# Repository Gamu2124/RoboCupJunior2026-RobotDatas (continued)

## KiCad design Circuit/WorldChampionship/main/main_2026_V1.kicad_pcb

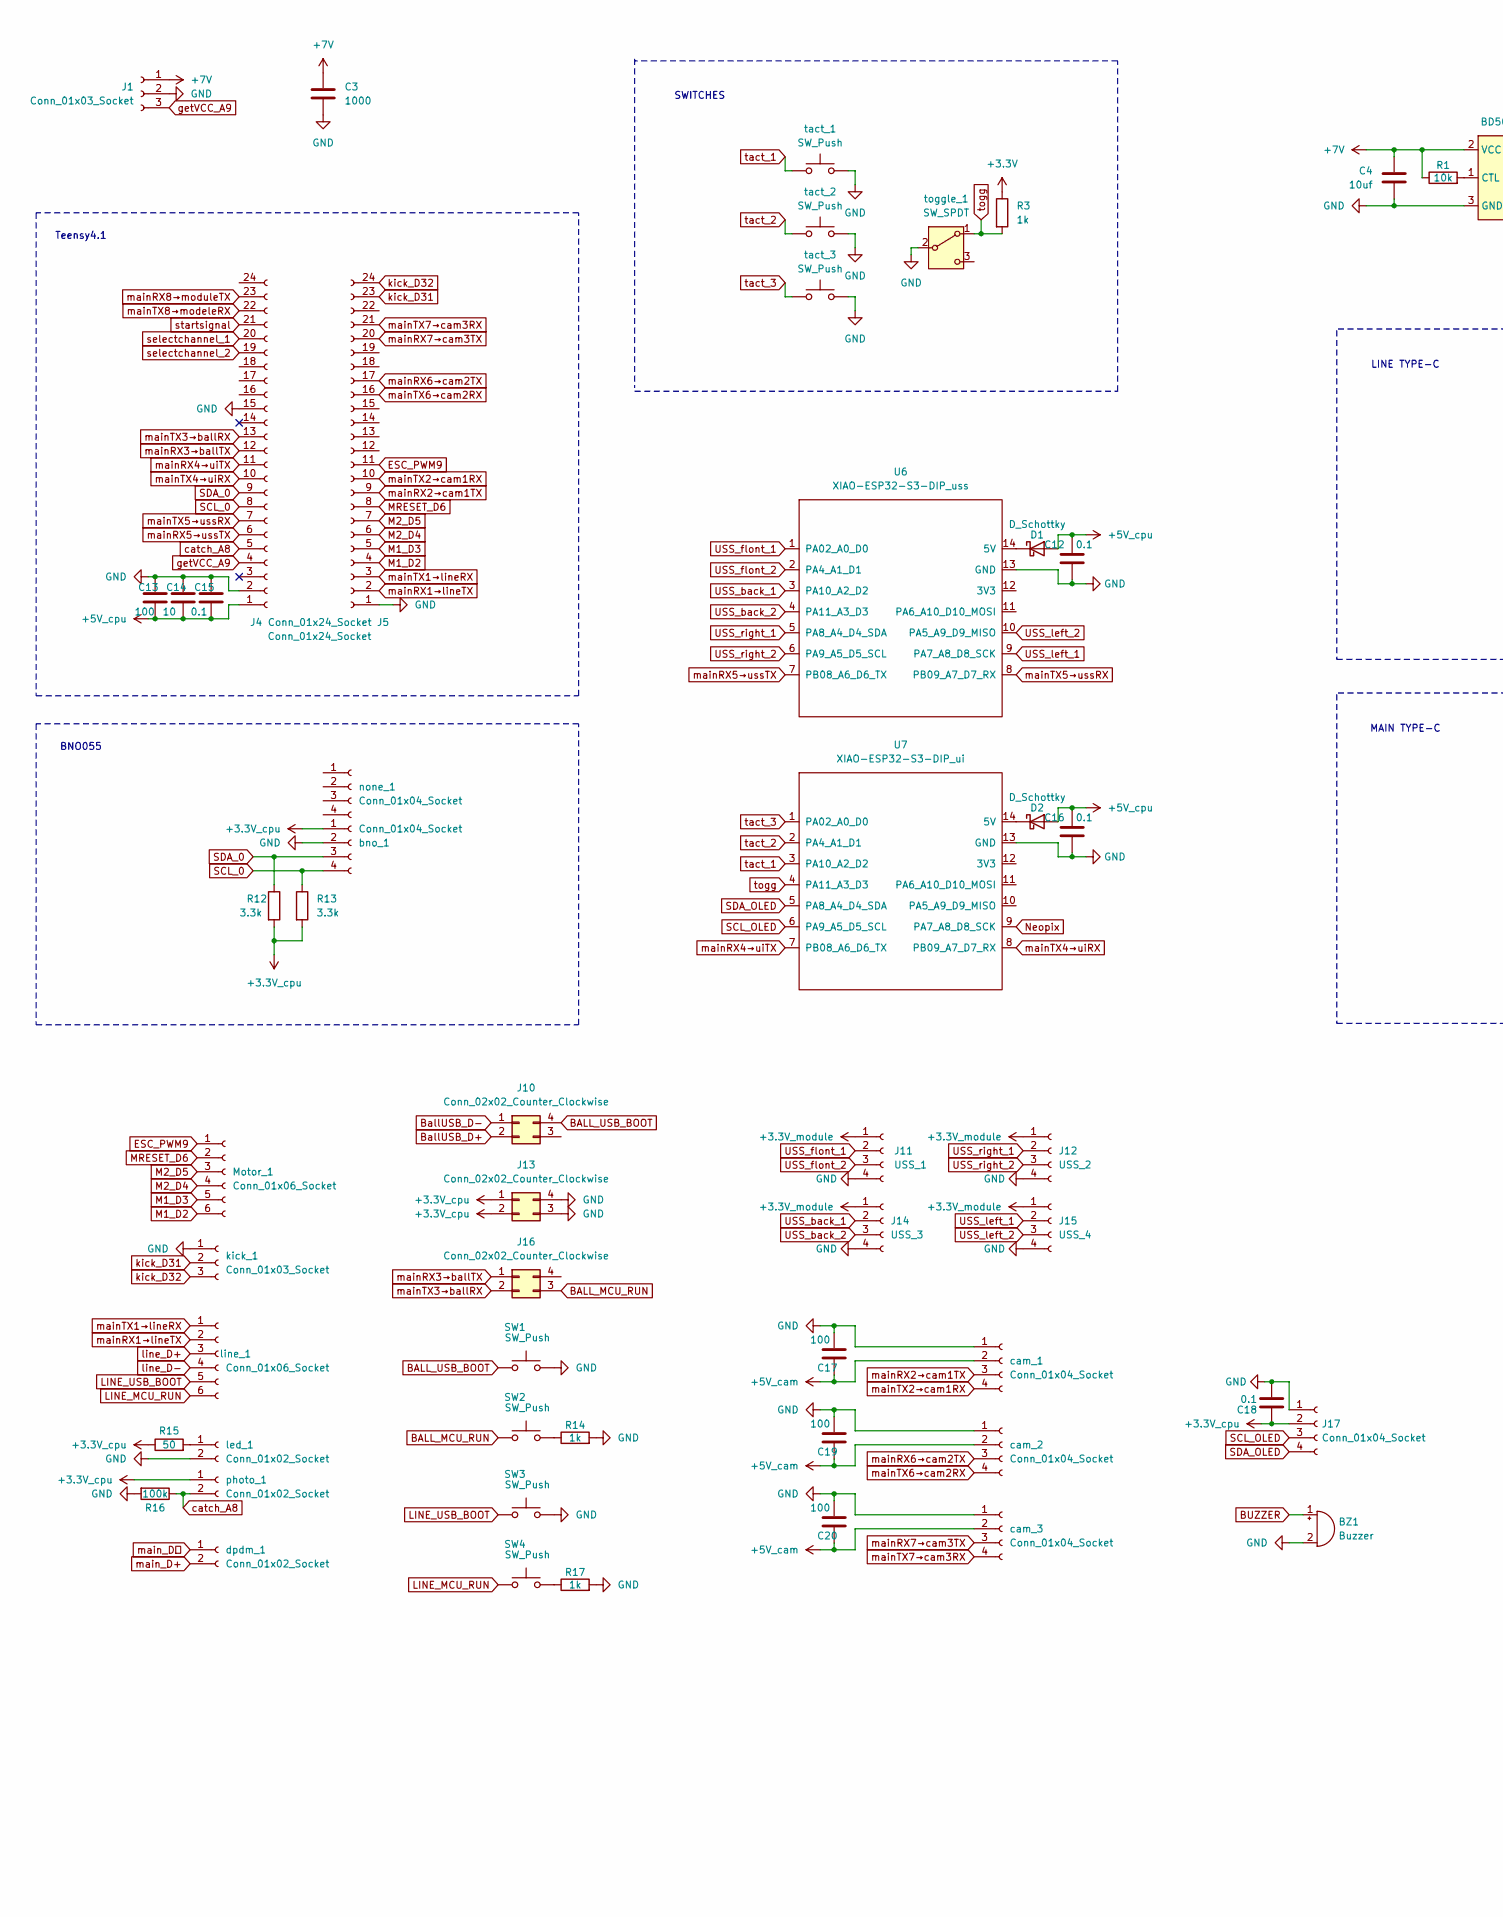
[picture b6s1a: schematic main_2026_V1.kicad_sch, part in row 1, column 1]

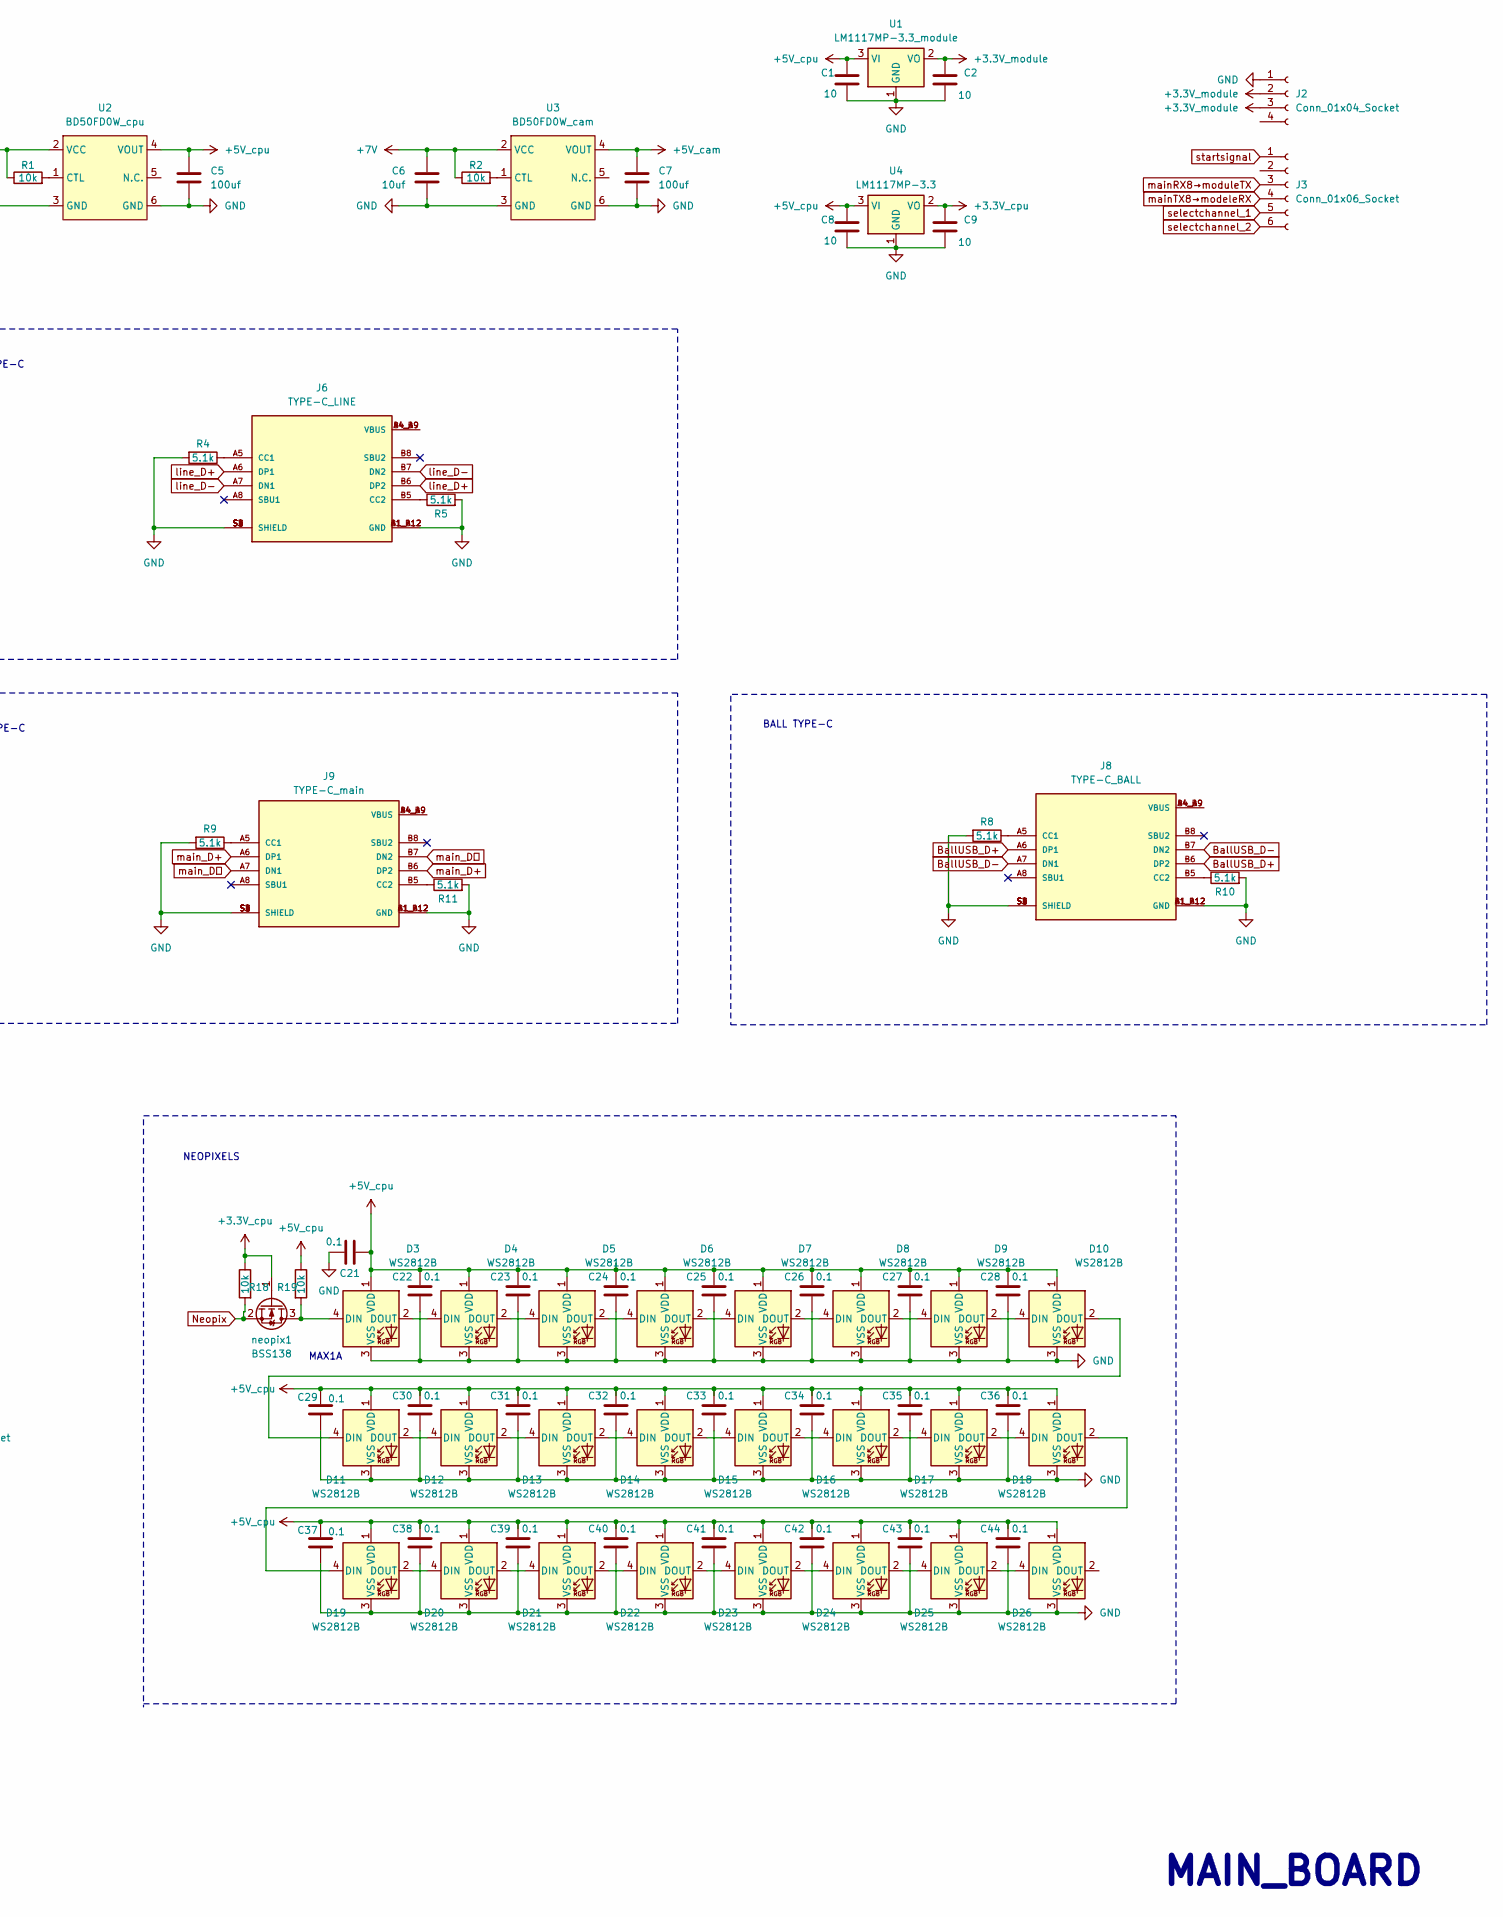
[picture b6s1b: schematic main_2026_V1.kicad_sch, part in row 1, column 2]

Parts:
BZ1: Buzzer; XDCR_KXG0909P
C1, C2, C8, C9, C14: 10; C_1206_3216Metric_Pad1.33x1.80mm_HandSolder
C3: 1000; CP_Radial_D10.0mm_P5.00mm
C4, C6: 10uf; C_1206_3216Metric_Pad1.33x1.80mm_HandSolder
C5, C7: 100uf; CP_Elec_6.3x5.4
C12, C16, C18, C22, C23, C24, C25, C26, C27, C28, C29, C30, C31, C32, C33, C34, C35, C36, C37, C38, C39, C40, C41, C42, C43, C44: 0.1; C_0603_1608Metric_Pad1.08x0.95mm_HandSolder; LCSC C1581
C13, C17, C19, C20: 100; CP_Elec_6.3x5.4
C15: 0.1; C_Disc_D5.0mm_W2.5mm_P2.50mm
C21: 0.1; C_0603_1608Metric_Pad1.08x0.95mm_HandSolder; LCSC C1848
D1, D2: D_Schottky; D_A-405_P10.16mm_Horizontal
D3, D4, D5, D6, D7, D8, D9, D10, D11, D12, D13, D14, D15, D16, D17, D18, D19, D20, D21, D22, D23, D24, D25, D26: WS2812B; LED_WS2812B_PLCC4_5.0x5.0mm_P3.2mm
J1: Conn_01x03_Socket; JST_XH_B3B-XH-A_1x03_P2.50mm_Vertical
J2, J17: Conn_01x04_Socket; PinSocket_1x04_P2.54mm_Vertical
J3: Conn_01x06_Socket; PinSocket_1x06_P2.54mm_Vertical
J4, J5: Conn_01x24_Socket; PinSocket_1x24_P2.54mm_Vertical
J6: TYPE-C_LINE; USB_C_Receptacle_XKB_U262-16XN-4BVC11; PARTREV B
J8: TYPE-C_BALL; USB_C_Receptacle_XKB_U262-16XN-4BVC11; PARTREV B
J9: TYPE-C_main; USB_C_Receptacle_XKB_U262-16XN-4BVC11; PARTREV B
J10, J13, J16: Conn_02x02_Counter_Clockwise; PinHeader_2x02_P2.54mm_Vertical
J11: USS_1; JST_XH_B4B-XH-A_1x04_P2.50mm_Vertical
J12: USS_2; JST_XH_B4B-XH-A_1x04_P2.50mm_Vertical
J14: USS_3; JST_XH_B4B-XH-A_1x04_P2.50mm_Vertical
J15: USS_4; JST_XH_B4B-XH-A_1x04_P2.50mm_Vertical
Motor_1: Conn_01x06_Socket; TE_84952-6_1x06-1MP_P1.0mm_Horizontal
R1, R2: 10k; R_Axial_DIN0207_L6.3mm_D2.5mm_P10.16mm_Horizontal
R3: 1k; R_Axial_DIN0207_L6.3mm_D2.5mm_P10.16mm_Horizontal
R4, R5, R8, R9, R10, R11: 5.1k; R_0603_1608Metric_Pad0.98x0.95mm_HandSolder; LCSC C26033
R12: 3.3k; R_Axial_DIN0207_L6.3mm_D2.5mm_P10.16mm_Horizontal
R13: 3.3k; R_Axial_DIN0207_L6.3mm_D2.5mm_P10.16mm_Horizontal; LCSC C22978
R14, R17: 1k; R_0603_1608Metric_Pad0.98x0.95mm_HandSolder; LCSC C22978
R15: 50; R_Axial_DIN0204_L3.6mm_D1.6mm_P5.08mm_Horizontal
R16: 100k; R_0603_1608Metric; LCSC C23098
R18, R19: 10k; R_1206_3216Metric; LCSC C1489
SW1, SW2, SW3, SW4: SW_Push; Switch_SKRPABE010
U1: LM1117MP-3.3_module; SOT-223
U2: BD50FD0W_cpu; DPAK172P1054X200-6N
U3: BD50FD0W_cam; DPAK172P1054X200-6N
U4: LM1117MP-3.3; SOT-223
U6: XIAO-ESP32-S3-DIP_uss; XIAO-ESP32-S3-DIP
U7: XIAO-ESP32-S3-DIP_ui; XIAO-ESP32-S3-DIP
bno_1: Conn_01x04_Socket; PinSocket_1x04_P2.54mm_Vertical
cam_1, cam_2, cam_3: Conn_01x04_Socket; SEEED_110990030
dpdm_1: Conn_01x02_Socket; PinSocket_1x02_P2.54mm_Vertical
kick_1: Conn_01x03_Socket; JST_XH_B3B-XH-A_1x03_P2.50mm_Vertical
led_1: Conn_01x02_Socket; JST_XH_B2B-XH-AM_1x02_P2.50mm_Vertical
line_1: Conn_01x06_Socket; TE_84952-6_1x06-1MP_P1.0mm_Horizontal
neopix1: BSS138; SOT-23; LCSC C192057
none_1: Conn_01x04_Socket; PinSocket_1x04_P2.54mm_Vertical
photo_1: Conn_01x02_Socket; JST_XH_B2B-XH-AM_1x02_P2.50mm_Vertical
tact_1, tact_2, tact_3: SW_Push; SW_PUSH-12mm
toggle_1: SW_SPDT; PinSocket_1x03_P2.54mm_Vertical

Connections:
+3.3V: R3.1
+3.3V_cpu: C9.1, C18.1, J13.1, J13.2, J17.2, R12.2, R13.2, R15.1, R18.1, U4.2 (VO), bno_1.1, neopix1.1 (G), photo_1.1
+3.3V_module: C2.1, J2.2, J2.3, J11.1, J12.1, J14.1, J15.1, U1.2 (VO)
+5V_cam: C7.1, C17.1, C19.1, C20.1, U3.4 (VOUT), cam_1.2, cam_2.2, cam_3.2
+5V_cpu: C1.1, C5.1, C8.1, C12.2, C13.2, C14.2, C15.2, C16.2, C21.2, C22.2, C23.2, C24.2, C25.2, C26.2, C27.2, C28.2, C29.2, C30.2, C31.2, C32.2, C33.2, C34.2, C35.2, C36.2, C37.2, C38.2, C39.2, C40.2, C41.2, C42.2, C43.2, C44.2, D1.2 (A), D2.2 (A), D3.1 (VDD), D4.1 (VDD), D5.1 (VDD), D6.1 (VDD), D7.1 (VDD), D8.1 (VDD), D9.1 (VDD), D10.1 (VDD), D11.1 (VDD), D12.1 (VDD), D13.1 (VDD), D14.1 (VDD), D15.1 (VDD), D16.1 (VDD), D17.1 (VDD), D18.1 (VDD), D19.1 (VDD), D20.1 (VDD), D21.1 (VDD), D22.1 (VDD), D23.1 (VDD), D24.1 (VDD), D25.1 (VDD), D26.1 (VDD), J4.1, R19.1, U1.3 (VI), U2.4 (VOUT), U4.3 (VI)
+7V: C3.1, C4.1, C6.1, J1.1, R1.1, R2.1, U2.2 (VCC), U3.2 (VCC)
BALL_MCU_RUN: J16.3, SW2.2
BALL_USB_BOOT: J10.4, SW1.2
BallUSB_D+: J8.A6 (DP1), J8.B6 (DP2), J10.2
BallUSB_D-: J8.A7 (DN1), J8.B7 (DN2), J10.1
ESC_PWM9: J5.11, Motor_1.1
GND: BZ1.2 (-), C1.2, C2.2, C3.2, C4.2, C5.2, C6.2, C7.2, C8.2, C9.2, C12.1, C13.1, C14.1, C15.1, C16.1, C17.2, C18.2, C19.2, C20.2, C21.1, C22.1, C23.1, C24.1, C25.1, C26.1, C27.1, C28.1, C29.1, C30.1, C31.1, C32.1, C33.1, C34.1, C35.1, C36.1, C37.1, C38.1, C39.1, C40.1, C41.1, C42.1, C43.1, C44.1, D3.3 (VSS), D4.3 (VSS), D5.3 (VSS), D6.3 (VSS), D7.3 (VSS), D8.3 (VSS), D9.3 (VSS), D10.3 (VSS), D11.3 (VSS), D12.3 (VSS), D13.3 (VSS), D14.3 (VSS), D15.3 (VSS), D16.3 (VSS), D17.3 (VSS), D18.3 (VSS), D19.3 (VSS), D20.3 (VSS), D21.3 (VSS), D22.3 (VSS), D23.3 (VSS), D24.3 (VSS), D25.3 (VSS), D26.3 (VSS), J1.2, J2.1, J4.2, J4.15, J5.1, J6.A1, J6.A1_B12 (GND), J6.A12, J6.B1, J6.B1_A12 (GND), J6.B12, J6.S1 (SHIELD), J6.S2 (SHIELD), J6.S3 (SHIELD), J6.S4 (SHIELD), J8.A1, J8.A1_B12 (GND), J8.A12, J8.B1, J8.B1_A12 (GND), J8.B12, J8.S1 (SHIELD), J8.S2 (SHIELD), J8.S3 (SHIELD), J8.S4 (SHIELD), J9.A1, J9.A1_B12 (GND), J9.A12, J9.B1, J9.B1_A12 (GND), J9.B12, J9.S1 (SHIELD), J9.S2 (SHIELD), J9.S3 (SHIELD), J9.S4 (SHIELD), J11.4, J12.4, J13.3, J13.4, J14.4, J15.4, J17.1, R4.2, R5.2, R8.2, R9.2, R10.2, R11.2, R14.2, R16.2, R17.2, SW1.1, SW3.1, U1.1 (GND), U2.3 (GND), U2.6 (GND), U3.3 (GND), U3.6 (GND), U4.1 (GND), U6.13 (GND), U7.13 (GND), bno_1.2, cam_1.1, cam_2.1, cam_3.1, kick_1.1, led_1.2, tact_1.2, tact_2.2, tact_3.2, toggle_1.2 (B)
LINE_MCU_RUN: SW4.2, line_1.6
LINE_USB_BOOT: SW3.2, line_1.5
M1_D2: J5.4, Motor_1.6
M1_D3: J5.5, Motor_1.5
M2_D4: J5.6, Motor_1.4
M2_D5: J5.7, Motor_1.3
MRESET_D6: J5.8, Motor_1.2
Neopix: R18.2, U7.9 (PA7_A8_D8_SCK), neopix1.2 (S)
unnamed: D1.1 (K), U6.14 (5V)
unnamed: D2.1 (K), U7.14 (5V)
unnamed: D3.4 (DIN), R19.2, neopix1.3 (D)
unnamed: D3.2 (DOUT), D4.4 (DIN)
unnamed: D4.2 (DOUT), D5.4 (DIN)
unnamed: D5.2 (DOUT), D6.4 (DIN)
unnamed: D6.2 (DOUT), D7.4 (DIN)
unnamed: D7.2 (DOUT), D8.4 (DIN)
unnamed: D8.2 (DOUT), D9.4 (DIN)
unnamed: D9.2 (DOUT), D10.4 (DIN)
unnamed: D10.2 (DOUT), D11.4 (DIN)
unnamed: D11.2 (DOUT), D12.4 (DIN)
unnamed: D12.2 (DOUT), D13.4 (DIN)
unnamed: D13.2 (DOUT), D14.4 (DIN)
unnamed: D14.2 (DOUT), D15.4 (DIN)
unnamed: D15.2 (DOUT), D16.4 (DIN)
unnamed: D16.2 (DOUT), D17.4 (DIN)
unnamed: D17.2 (DOUT), D18.4 (DIN)
unnamed: D18.2 (DOUT), D19.4 (DIN)
unnamed: D19.2 (DOUT), D20.4 (DIN)
unnamed: D20.2 (DOUT), D21.4 (DIN)
unnamed: D21.2 (DOUT), D22.4 (DIN)
unnamed: D22.2 (DOUT), D23.4 (DIN)
unnamed: D23.2 (DOUT), D24.4 (DIN)
unnamed: D24.2 (DOUT), D25.4 (DIN)
unnamed: D25.2 (DOUT), D26.4 (DIN)
unnamed: J6.A5 (CC1), R4.1
unnamed: J6.B5 (CC2), R5.1
unnamed: J8.A5 (CC1), R8.1
unnamed: J8.B5 (CC2), R10.1
unnamed: J9.A5 (CC1), R9.1
unnamed: J9.B5 (CC2), R11.1
unnamed: R14.1, SW2.1
unnamed: R17.1, SW4.1
unnamed: R1.2, U2.1 (CTL)
unnamed: R2.2, U3.1 (CTL)
unnamed: R15.2, led_1.1
SCL_0: J4.8, R13.1, bno_1.4
SCL_OLED: J17.3, U7.6 (PA9_A5_D5_SCL)
SDA_0: J4.9, R12.1, bno_1.3
SDA_OLED: J17.4, U7.5 (PA8_A4_D4_SDA)
USS_back_1: J14.2, U6.3 (PA10_A2_D2)
USS_back_2: J14.3, U6.4 (PA11_A3_D3)
USS_flont_1: J11.2, U6.1 (PA02_A0_D0)
USS_flont_2: J11.3, U6.2 (PA4_A1_D1)
USS_left_1: J15.2, U6.9 (PA7_A8_D8_SCK)
USS_left_2: J15.3, U6.10 (PA5_A9_D9_MISO)
USS_right_1: J12.2, U6.5 (PA8_A4_D4_SDA)
USS_right_2: J12.3, U6.6 (PA9_A5_D5_SCL)
catch_A8: J4.5, R16.1, photo_1.2
getVCC_A9: J1.3, J4.4
kick_D31: J5.23, kick_1.2
kick_D32: J5.24, kick_1.3
line_D+: J6.A6 (DP1), J6.B6 (DP2), line_1.3
line_D-: J6.A7 (DN1), J6.B7 (DN2), line_1.4
mainRX1→lineTX: J5.2, line_1.2
mainRX2→cam1TX: J5.9, cam_1.3
mainRX3→ballTX: J4.12, J16.1
mainRX4→uiTX: J4.11, U7.7 (PB08_A6_D6_TX)
mainRX5→ussTX: J4.6, U6.7 (PB08_A6_D6_TX)
mainRX6→cam2TX: J5.17, cam_2.3
mainRX7→cam3TX: J5.20, cam_3.3
mainRX8→moduleTX: J3.3, J4.23
mainTX1→lineRX: J5.3, line_1.1
mainTX2→cam1RX: J5.10, cam_1.4
mainTX3→ballRX: J4.13, J16.2
mainTX4→uiRX: J4.10, U7.8 (PB09_A7_D7_RX)
mainTX5→ussRX: J4.7, U6.8 (PB09_A7_D7_RX)
mainTX6→cam2RX: J5.16, cam_2.4
mainTX7→cam3RX: J5.21, cam_3.4
mainTX8→modeleRX: J3.4, J4.22
main_D+: J9.A6 (DP1), J9.B6 (DP2), dpdm_1.2
main_Dー: J9.A7 (DN1), J9.B7 (DN2), dpdm_1.1
selectchannel_1: J3.5, J4.20
selectchannel_2: J3.6, J4.19
startsignal: J3.1, J4.21
tact_1: U7.3 (PA10_A2_D2), tact_1.1
tact_2: U7.2 (PA4_A1_D1), tact_2.1
tact_3: U7.1 (PA02_A0_D0), tact_3.1
togg: R3.2, U7.4 (PA11_A3_D3), toggle_1.1 (A)

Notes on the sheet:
SWITCHES
LINE TYPE-C
BNO055
BALL TYPE-C
Teensy4.1
NEOPIXELS
MAIN TYPE-C
MAX1A
MAIN_BOARD

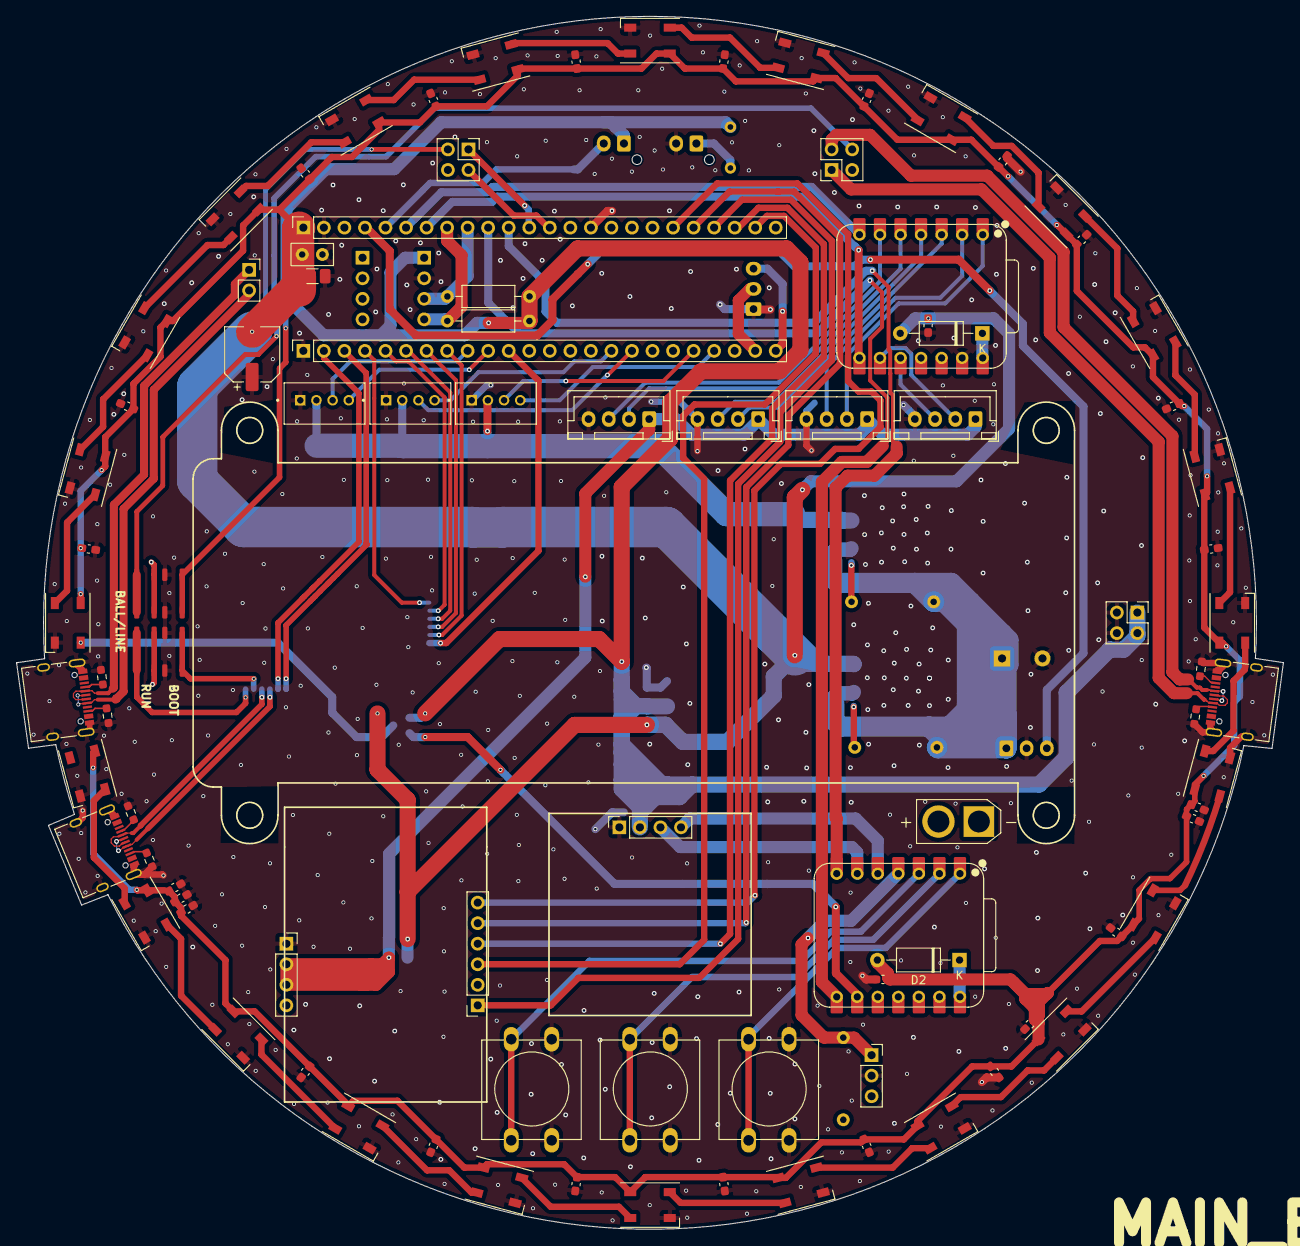
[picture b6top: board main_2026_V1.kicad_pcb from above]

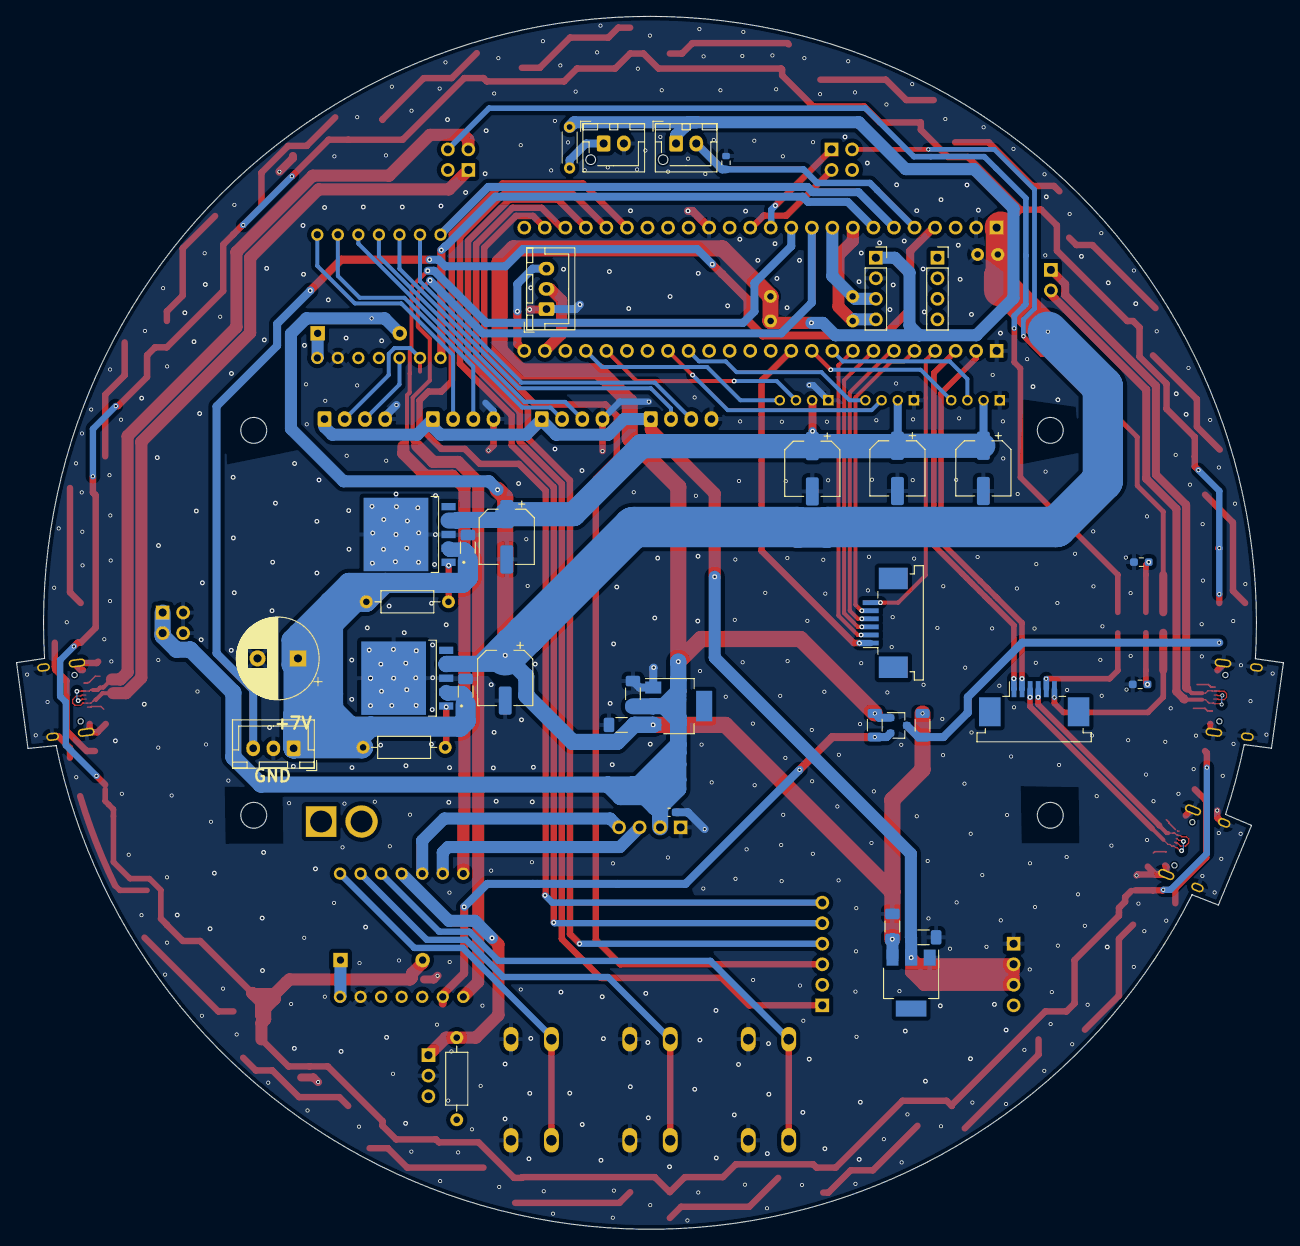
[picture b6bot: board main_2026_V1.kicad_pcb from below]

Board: 2 copper layers, 156.7 x 150.0 mm, 127 parts (35 on the bottom side), 99 nets.

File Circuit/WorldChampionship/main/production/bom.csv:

Designator,Footprint,Quantity,Value,LCSC Part #
"BNO_1, J17, J2, NONE_1",PinSocket_1x04_P2.54mm_Vertical,4,Conn_01x04_Socket,
"C1, C14, C2, C8, C9",1206,5,10,
"C12, C16, C18, C22, C23, C24, C25, C26, C27, C28, C29, C30, C31, C32, C33, C34, C35, C36, C37, C38, C39, C40, C41, C42, C43, C44",0603,26,0.1,C1581
"C13, C17, C19, C20",CP_Elec_6.3x5.4,4,100,
C15,C_Disc_D5.0mm_W2.5mm_P2.50mm,1,0.1,
C21,0603,1,0.1,C1848 
C3,CP_Radial_D10.0mm_P5.00mm,1,1000,
"C4, C6",1206,2,10uf,
"C5, C7",CP_Elec_6.3x5.4,2,100uf,
"CAM_1, CAM_2, CAM_3",SEEED_110990030,3,Conn_01x04_Socket,
"D1, D2",D_A-405_P10.16mm_Horizontal,2,D_Schottky,
"D10, D11, D12, D13, D14, D15, D16, D17, D18, D19, D20, D21, D22, D23, D24, D25, D26, D3, D4, D5, D6, D7, D8, D9",LED_WS2812B_PLCC4_5.0x5.0mm_P3.2mm,24,WS2812B,
DPDM_1,PinSocket_1x02_P2.54mm_Vertical,1,Conn_01x02_Socket,
"J1, KICK_1",JST_XH_B3B-XH-A_1x03_P2.50mm_Vertical,2,Conn_01x03_Socket,
"J10, J13, J16",PinHeader_2x02_P2.54mm_Vertical,3,Conn_02x02_Counter_Clockwise,
J11,JST_XH_B4B-XH-A_1x04_P2.50mm_Vertical,1,USS_1,
J12,JST_XH_B4B-XH-A_1x04_P2.50mm_Vertical,1,USS_2,
J14,JST_XH_B4B-XH-A_1x04_P2.50mm_Vertical,1,USS_3,
J15,JST_XH_B4B-XH-A_1x04_P2.50mm_Vertical,1,USS_4,
J3,PinSocket_1x06_P2.54mm_Vertical,1,Conn_01x06_Socket,
"J4, J5",PinSocket_1x24_P2.54mm_Vertical,2,Conn_01x24_Socket,
J6,USB_C_Receptacle_XKB_U262-16XN-4BVC11,1,TYPE-C_LINE,
J8,USB_C_Receptacle_XKB_U262-16XN-4BVC11,1,TYPE-C_BALL,
J9,USB_C_Receptacle_XKB_U262-16XN-4BVC11,1,TYPE-C_main,
"LED_1, PHOTO_1",JST_XH_B2B-XH-AM_1x02_P2.50mm_Vertical,2,Conn_01x02_Socket,
"LINE_1, MOTOR_1",TE_84952-6_1x06-1MP_P1.0mm_Horizontal,2,Conn_01x06_Socket,
NEOPIX1,SOT-23,1,BSS138, C192057
"R1, R2",R_Axial_DIN0207_L6.3mm_D2.5mm_P10.16mm_Horizontal,2,10k,
"R10, R11, R4, R5, R8, R9",0603,6,5.1k,C26033
R12,R_Axial_DIN0207_L6.3mm_D2.5mm_P10.16mm_Horizontal,1,3.3k,
R13,R_Axial_DIN0207_L6.3mm_D2.5mm_P10.16mm_Horizontal,1,3.3k,C22978
"R14, R17",0603,2,1k,C22978
R15,R_Axial_DIN0204_L3.6mm_D1.6mm_P5.08mm_Horizontal,1,50,
R16,0603,1,100k,C23098
"R18, R19",1206,2,10k, C1489
R3,R_Axial_DIN0207_L6.3mm_D2.5mm_P10.16mm_Horizontal,1,1k,
"SW1, SW2, SW3, SW4",Switch_SKRPABE010,4,SW_Push,
"TACT_1, TACT_2, TACT_3",SW_PUSH-12mm,3,SW_Push,
TOGGLE_1,PinSocket_1x03_P2.54mm_Vertical,1,SW_SPDT,
U1,SOT-223,1,LM1117MP-3.3_module,
U2,DPAK172P1054X200-6N,1,BD50FD0W_cpu,
U3,DPAK172P1054X200-6N,1,BD50FD0W_cam,
U4,SOT-223,1,LM1117MP-3.3,
U6,XIAO-ESP32-S3-DIP,1,XIAO-ESP32-S3-DIP_uss,
U7,XIAO-ESP32-S3-DIP,1,XIAO-ESP32-S3-DIP_ui,

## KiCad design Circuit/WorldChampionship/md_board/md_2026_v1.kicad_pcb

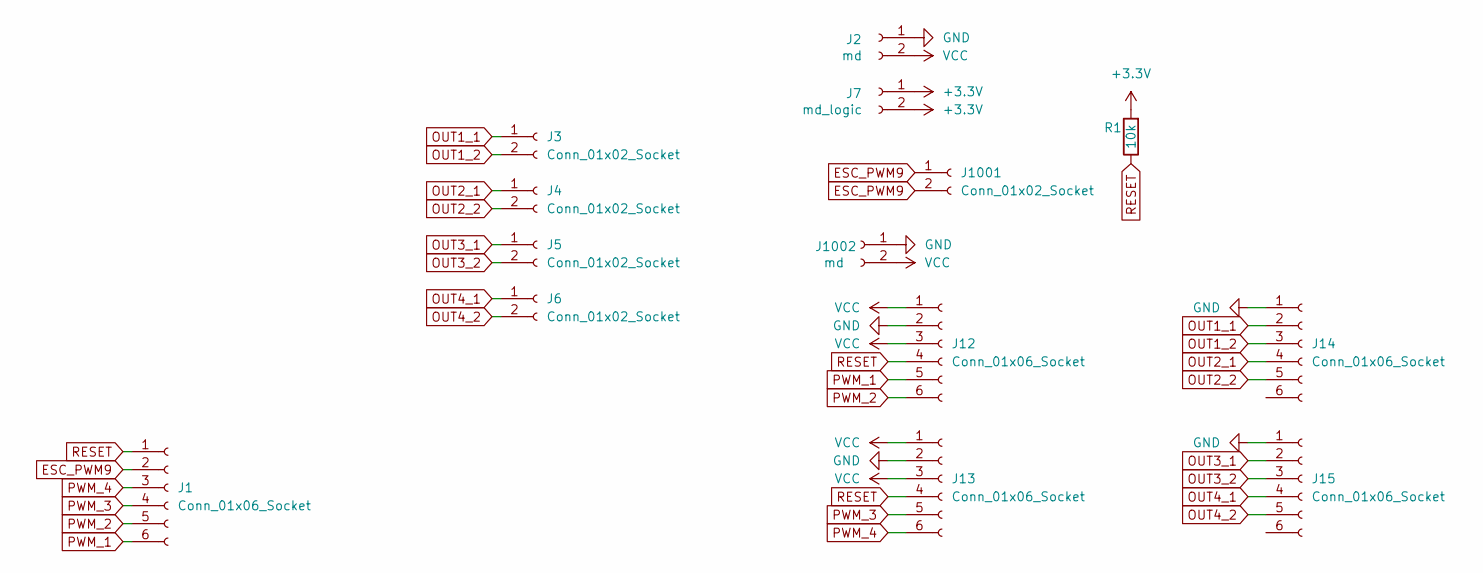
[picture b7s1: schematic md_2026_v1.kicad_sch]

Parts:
J1: Conn_01x06_Socket; TE_84952-6_1x06-1MP_P1.0mm_Horizontal
J2, J1002: md; AMASS_XT30U-M_1x02_P5.0mm_Vertical
J3, J4, J5, J6: Conn_01x02_Socket; JST_XH_S2B-XH-A_1x02_P2.50mm_Horizontal
J7: md_logic; JST_XH_B2B-XH-A_1x02_P2.50mm_Vertical
J12, J13, J14, J15: Conn_01x06_Socket; PinSocket_1x06_P2.54mm_Vertical
J1001: Conn_01x02_Socket; JST_XH_B2B-XH-A_1x02_P2.50mm_Vertical
R1: 10k; R_Axial_DIN0207_L6.3mm_D2.5mm_P10.16mm_Horizontal; LCSC C15401

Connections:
+3.3V: J7.1, J7.2, R1.2
ESC_PWM9: J1.2, J1001.1, J1001.2
GND: J2.1, J12.2, J13.2, J14.1, J15.1, J1002.1
OUT1_1: J3.1, J14.2
OUT1_2: J3.2, J14.3
OUT2_1: J4.1, J14.4
OUT2_2: J4.2, J14.5
OUT3_1: J5.1, J15.2
OUT3_2: J5.2, J15.3
OUT4_1: J6.1, J15.4
OUT4_2: J6.2, J15.5
PWM_1: J1.6, J12.5
PWM_2: J1.5, J12.6
PWM_3: J1.4, J13.5
PWM_4: J1.3, J13.6
RESET: J1.1, J12.4, J13.4, R1.1
VCC: J2.2, J12.1, J12.3, J13.1, J13.3, J1002.2

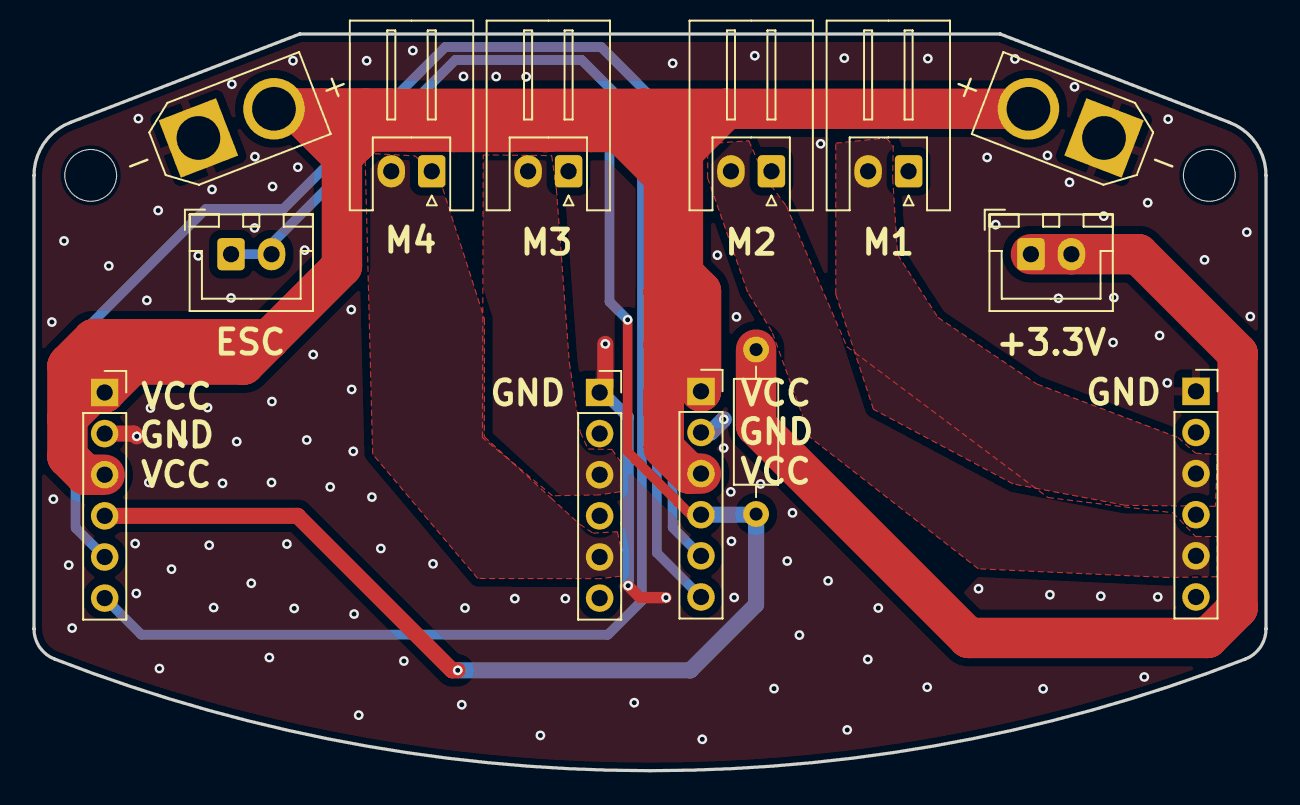
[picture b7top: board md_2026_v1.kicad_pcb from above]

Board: 2 copper layers, 76.1 x 45.5 mm, 16 parts (1 on the bottom side), 17 nets.

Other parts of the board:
H1, H1#2: MountingHole; MountingHole_3.2mm_M3

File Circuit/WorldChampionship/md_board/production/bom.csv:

Designator,Footprint,Quantity,Value,LCSC Part #
J1,TE_84952-6_1x06-1MP_P1.0mm_Horizontal,1,Conn_01x06_Socket,
J1001,JST_XH_B2B-XH-A_1x02_P2.50mm_Vertical,1,Conn_01x02_Socket,
"J1002, J2",AMASS_XT30U-M_1x02_P5.0mm_Vertical,2,md,
"J12, J13, J14, J15",PinSocket_1x06_P2.54mm_Vertical,4,Conn_01x06_Socket,
"J3, J4, J5, J6",JST_XH_S2B-XH-A_1x02_P2.50mm_Horizontal,4,Conn_01x02_Socket,
J7,JST_XH_B2B-XH-A_1x02_P2.50mm_Vertical,1,md_logic,
R1,R_Axial_DIN0207_L6.3mm_D2.5mm_P10.16mm_Horizontal,1,10k,C15401
